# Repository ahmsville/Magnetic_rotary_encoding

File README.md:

# Magnetic_Rotary_Encoding

## Learn more about this project - 
 - https://www.ahmsvillelabs.io/projects/magnetic-rotary-encoding
 - https://youtu.be/atb6d4b-VYk
 - https://youtu.be/_1tGosBLRB0

## BUILD INSTRUCTIONS
 - https://www.ahmsvillelabs.io/magnetic-rotary-encoderbuild

# Hardware Options

 ## 1. Magnetic Rotary Encoder 
 This is standalone encoder made to connect to a seperate microcontroller like an Arduino board, this version has a base resolution of 72, extendable up to 72000 steps per revolution.

 ### Features:
- Capacitive touch / button input
- Addressable Led ring (18 LEDs)
 ### Supported Boards / Platform:
- **All Arduino Boards** 
- **Raspberry Pi Pico C/C++ SDK** 
- **All Micropython-Supported Boards**

## 2. Magnetic Rotary Encoder MINI 
 This is standalone encoder similar to the first option, only with a small form factor, this version has a base resolution of 36, extendable up to 36000 steps per revolution.

  ### Features:
- Capacitive touch / button input
- Addressable Led ring (12 LEDs)
 ### Supported Boards / Platform:
- **All Arduino Boards** 
- **Raspberry Pi Pico C/C++ SDK** 
- **All Micropython-Supported Boards**

## [3. Pico Dev M3](https://github.com/ahmsville/Magnetic_rotary_encoding/tree/master/PICO%20DEV%20M3) 
 This is a full fledged development board combined with the magnetic rotary encoder, its built with the Raspberry Pi RP2040 microcontroller chip with a base resolution of 36, extendable up to 36000 steps per revolution.

  ### Features:
- RP2040 chip, Dual-core Arm Cortex-M0+ processor at 133 MHz
- 264kB on-chip SRAM
- 128Mb on-board QSPI flash
- 19 multifunction GPIO pins, with 2 analog inputs
- 2 UARTs
- 2 SPI controllers
- 2 I2C controllers
- 16 PWM channels
- USB 1.1 controller with host and device support
- 8 PIO state machines
- USB type C
- Lipo charging
- onboard Button input
- Addressable Led ring (18 LEDs)
 ### Supported Platform:
- **RP2040 C/C++ SDK** 
- **Micropython**

# How to connect and use the [Ahmsville labs magnetic rotary encoder](https://www.tindie.com/products/22156/).

There are three ways to connect the magnetic rotary encoder, all with their benefits and draw backs.

## 1. Analog only Detection: 

in this mode the library uses just the signals from the hall effect sensors to make sense of the rotation of the encoder. the benefit of this mode is that you only need two analog pins to do all the rotation encoding, also been analog means you can use the libraries built in interpolation mode for an extremely high and granular resolution. The drawback is, this mode requires constant polling of the sensors which is not ideal for a complex system, also if the board does not have analog pins or if your setup cannot spare any of them, then you cannot use this mode.

## Connection

To use this mode, simply connect ENC-1 and ENC-2 to two analog input pins, you may also connect the LED pin to any available pin on the board. VCC  should be connected to the same voltage level used by the microcontroller on the boards, so power the encoder with 5v if the board uses 5v, and power it with 3.3v it the board uses 3.3v, you should offcus also connect the GND pin.

## Code

To test the example code, all you have to do is activate the analog only mode and change the pin assignment according to your connections. For the mode, you have the option to choose continuous rotation detection which returns a continuous count in either direction, or absolute positioning, which returns a value within the encoder’s base resolution, you can also choose the extended interpolated resolution mode for a super-duper high resolution.

## C/C++

```c++
#define ENCMODE 1 // BASE RESOLUTION ANALOG ONLY
//#define ENCMODE 2 // BASE RESOLUTION ANALOG ONLY ABSOLUTE POSITIONING
//#define ENCMODE 3 // EXTENDED RESOLUTION ANALOG ONLY
//#define ENCMODE 4 // BASE RESOLUTION ANALOG AND DIGITAL
//#define ENCMODE 5 // BASE RESOLUTION ANALOG AND DIGITAL ABSOLUTE POSITIONING
//#define ENCMODE 6 // EXTENDED RESOLUTION ANALOG AND DIGITAL
//#define ENCMODE 7 // BASE RESOLUTION DIGITAL ONLY
//#define ENCMODE 8 // BASE RESOLUTION DIGITAL ONLY ABSOLUTE POSITIONING
```

```c++
#define E1_ADC_PIN 26 // ADC PIN for hall sensor 1
#define E2_ADC_PIN 27 // ADC PIN for hall sensor 2
```

## MicroPython

```python
ENCMODE = 1 # BASE RESOLUTION ANALOG ONLY
#ENCMODE  = 2 # BASE RESOLUTION ANALOG ONLY ABSOLUTE POSITIONING
#ENCMODE  = 3 # EXTENDED RESOLUTION ANALOG ONLY
#ENCMODE  = 4 # BASE RESOLUTION ANALOG AND DIGITAL
#ENCMODE  = 5 # BASE RESOLUTION ANALOG AND DIGITAL ABSOLUTE POSITIONING
#ENCMODE  = 6 # EXTENDED RESOLUTION ANALOG AND DIGITAL
#ENCMODE  = 7 # BASE RESOLUTION DIGITAL ONLY
#ENCMODE  = 8 # BASE RESOLUTION DIGITAL ONLY ABSOLUTE POSITIONING
```

```python
E1_ADC_PIN = 26  # ADC PIN for hall sensor 1
E2_ADC_PIN = 27  # ADC PIN for hall sensor 2
```

## 2. Analog and Digital Detection: 

in this mode the library uses the signals from the hall effect sensors together with two additional digital interrupt enabled input pins. This mode has all the same features and benefits as the analog only detection mode without the need for constant polling of the hall effect sensors, this is extremely usefull for complex systems, as the interrupt pins notify the code of when a rotation occurs, so constant polling is not needed, this mode is in fact the mode used on the [Ahmsville Dial V2](https://youtu.be/yGbshYLfDnc).
Please note that the code will return to constant polling if you select the Extended Resolution mode, since this process requires interpolation between the encoder’s steps.

## Connection

To use this mode, simply connect ENC-1 and ENC-2 to two analog input pins, and E1-INT1 and E2-INT1 to two interrupt enabled pins on the board, you may also connect the LED pin to any available pins on the board. VCC  should be connected to the same voltage level used by the microcontroller on the boards, so power the encoder with 5v if the board uses 5v, and power it with 3.3v it the board uses 3.3v, you should offcus also connect the GND pin.

Depending on your encoder version, you may also need to bridge the config pads on the PCB to use this mode.

## Code

To test the code, all you have to do is activate the analog and digital mode and also change the pin assignment according to your connections. For this mode, you also have the option to choose continuous rotation detection which returns a continuous count in either direction, or absolute positioning, which returns a value within the encoder’s base resolution, you can also choose the extended interpolated resolution mode for a super-duper high resolution.

## C/C++

```c++
//#define ENCMODE 1 // BASE RESOLUTION ANALOG ONLY
//#define ENCMODE 2 // BASE RESOLUTION ANALOG ONLY ABSOLUTE POSITIONING
//#define ENCMODE 3 // EXTENDED RESOLUTION ANALOG ONLY
#define ENCMODE 4 // BASE RESOLUTION ANALOG AND DIGITAL
//#define ENCMODE 5 // BASE RESOLUTION ANALOG AND DIGITAL ABSOLUTE POSITIONING
//#define ENCMODE 6 // EXTENDED RESOLUTION ANALOG AND DIGITAL
//#define ENCMODE 7 // BASE RESOLUTION DIGITAL ONLY
//#define ENCMODE 8 // BASE RESOLUTION DIGITAL ONLY ABSOLUTE POSITIONING
```

```c++
#define E1_INT1 16 // hall sensor 1 interrupt pin 1
#define E2_INT1 18 // hall sensor 2 interrupt pin 1

#define E1_ADC_PIN 26 // ADC PIN for hall sensor 1
#define E2_ADC_PIN 27 // ADC PIN for hall sensor 2
```

## MicroPython

```python
#ENCMODE = 1 # BASE RESOLUTION ANALOG ONLY
#ENCMODE  = 2 # BASE RESOLUTION ANALOG ONLY ABSOLUTE POSITIONING
#ENCMODE  = 3 # EXTENDED RESOLUTION ANALOG ONLY
ENCMODE  = 4 # BASE RESOLUTION ANALOG AND DIGITAL
#ENCMODE  = 5 # BASE RESOLUTION ANALOG AND DIGITAL ABSOLUTE POSITIONING
#ENCMODE  = 6 # EXTENDED RESOLUTION ANALOG AND DIGITAL
#ENCMODE  = 7 # BASE RESOLUTION DIGITAL ONLY
#ENCMODE  = 8 # BASE RESOLUTION DIGITAL ONLY ABSOLUTE POSITIONING
```

```python
E1_INT1 = 16 # hall sensor 1 interrupt pin 1
E2_INT1 = 18 # hall sensor 2 interrupt pin 1

E1_ADC_PIN = 26 # ADC PIN for hall sensor 1
E2_ADC_PIN = 27 # ADC PIN for hall sensor 2
```

## 3. Digital only Detection: 

in this mode the library uses only digital interrupt enabled input pins; four of them. This mode is similar in operation to traditional rotary switches, the analog signals from the hall effect sensors have been converted to digital signals using comparators, so no analog input pins are required. This mode was developed for systems that don’t have or cannot spare analog input pins, its also the fastest mode and requires zero polling, which is why I used it to encode the [Pick N Place Wheel](https://youtu.be/MtNO8-5vCqg). 
Because this mode uses digital signals alone, you cannot use the interpolated extended resolution mode that is available in the previous modes.

## Connection

To use this mode, simply connect E1-INT1, E1-INT2, E2-INT1 and E2-INT2 to four interrupt enabled pins on the board, you may also connect the LED pin to any available pins on the board. VCC  should be connected to the same voltage level used by the microcontroller on the boards, so power the encoder with 5v if the board uses 5v, and power it with 3.3v it the board uses 3.3v,  also connect the GND pin.

## Code

To test the code, all you have to do is activate the digital only mode and also change the pin assignments according to your connections. For this mode, you have the option to choose continuous rotation detection which returns a continuous count in either direction, or absolute positioning, which returns a value within the encoder’s base resolution.

## C/C++

```c++
//#define ENCMODE 1 // BASE RESOLUTION ANALOG ONLY
//#define ENCMODE 2 // BASE RESOLUTION ANALOG ONLY ABSOLUTE POSITIONING
//#define ENCMODE 3 // EXTENDED RESOLUTION ANALOG ONLY
//#define ENCMODE 4 // BASE RESOLUTION ANALOG AND DIGITAL
//#define ENCMODE 5 // BASE RESOLUTION ANALOG AND DIGITAL ABSOLUTE POSITIONING
//#define ENCMODE 6 // EXTENDED RESOLUTION ANALOG AND DIGITAL
#define ENCMODE 7 // BASE RESOLUTION DIGITAL ONLY
//#define ENCMODE 8 // BASE RESOLUTION DIGITAL ONLY ABSOLUTE POSITIONING
```

```c++
#define E1_INT1 16 // hall sensor 1 interrupt pin 1
#define E1_INT2 17 // hall sensor 1 interrupt pin 2
#define E2_INT1 18 // hall sensor 2 interrupt pin 1
#define E2_INT2 19 // hall sensor 2 interrupt pin 2
```

## MicroPython

```python
#ENCMODE = 1 # BASE RESOLUTION ANALOG ONLY
#ENCMODE  = 2 # BASE RESOLUTION ANALOG ONLY ABSOLUTE POSITIONING
#ENCMODE  = 3 # EXTENDED RESOLUTION ANALOG ONLY
ENCMODE  = 4 # BASE RESOLUTION ANALOG AND DIGITAL
#ENCMODE  = 5 # BASE RESOLUTION ANALOG AND DIGITAL ABSOLUTE POSITIONING
#ENCMODE  = 6 # EXTENDED RESOLUTION ANALOG AND DIGITAL
#ENCMODE  = 7 # BASE RESOLUTION DIGITAL ONLY
#ENCMODE  = 8 # BASE RESOLUTION DIGITAL ONLY ABSOLUTE POSITIONING
```

```python
E1_INT1 = 16  # hall sensor 1 interrupt pin 1
E1_INT2 = 17  # hall sensor 1 interrupt pin 2
E2_INT1 = 18  # hall sensor 2 interrupt pin 1
E2_INT2 = 19  # hall sensor 2 interrupt pin 2
```

# Complimentary Input on the Encoder

You have two options when it comes to complimentary input on the encoder, you can choose to use capacitive touch or a normal push button, both the capacitive touch and the push button will be included with the kit if you buy it from [my store](https://www.tindie.com/products/22156/).
To use capacitive touch, you will need an Arduino board, if you use other development boards like the ESP32 or Raspberry PI Pico, you will have to use the push button.

## Capacitive touch
To use the capacitive touch on an Arduino, you must have assembled the encoder according to the instructions, so that you can simply connect CT1 and CT2 to two available pins and then update the pin assignment in the example code accordingly.

## C/C++

```c++
#define CT1 5 // CAPACITIVE TOUCH (CT1)
#define CT2 6 // CAPACITIVE TOUCH (CT2)
```

## Push button
To use the push button, you should solder the included button to the encoder board and then connect only CT1 to an available pin on the development board.

## C/C++

```c++
#define CT1 15 // PUSH BUTTON (CT1)
```

## MicroPython

```python
CT1 = 15 # PUSH BUTTON (CT1)
```

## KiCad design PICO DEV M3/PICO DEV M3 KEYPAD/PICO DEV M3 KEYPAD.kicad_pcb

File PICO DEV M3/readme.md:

# PICO DEV M3

The **Pico Dev M3** is a development board based on Raspberry Pi's **RP2040 microcontrolle**r chip, the board is also a high-resolution **magnetic rotary encoder** when paired with a few 3D printed parts, which makes this the perfect board for applications and projects that can benefit from having a rotary encoder, a good example is making macro pads, and other similar secondary controllers.

## **Board Features**
- RP2040 chip, Dual-core Arm Cortex-M0+ processor at 133 MHz
- 264kB on-chip SRAM
- 128Mb on-board QSPI flash
- 19 multifunction GPIO pins, with 2 analog inputs
- 2 UARTs
- 2 SPI controllers
- 2 I2C controllers
- 16 PWM channels
- USB 1.1 controller with host and device support
- 8 PIO state machines
- USB type C
- Lipo charging
- onboard Button input
- Addressable Led ring (18 LEDs)

## **Encoder Features**

- The onboard encoder features a base resolution of **36 steps, extending up to 36000** steps per revolution.
- There’s also a ring of **18 individually addressable LEDs** on board.
- Features a ball bearing which gives the encoder a significantly smoother feel compared to traditional rotary encoders.
- Customizable 3d printed encoder. 
- Implementing the encoder is also really straightforward using the dedicated Libraries and Sample Codes
- Easy mounting options

### **Programming Language:**

- **RP2040 C/C++ SDK** 
- **Micropython**

## **Sample Projects Based on the PICO DEV M3:**

- **Pico Dev M3 Keypad** 

This is a 12-key macropod that uses the Pico dev m3 as its controller, the breakout board features backlit keys, headers for connecting I2C, SPI, and UART peripherals, and a header for connecting a joystick module to the Pico dev m3, you can power the keypad from the type c port on the pico dev m3 board or with a Lipo battery connected to the BAT header, taking advantage of the Lipo charge controller built into the pico dev m3.
- **PIO Stepper Controller**

This breakout board allows you to use this Programmable IO (PIO) on the RP2040 chip on the Pico dev m3 to individually control 3 stepper motors. This board can be used to control any 3-axis motion system, robot, or custom mechanism.

## BUILD INSTRUCTIONS
 - https://www.ahmsvillelabs.io/magnetic-rotary-encoderbuild/pico-dev-m3

### **Encoder Assembly:**

- Sandwich the pico dev m3 board between the **BOARD BUTTON** and **BOARD TOP** 3D printed parts, and secure them together using 3 **M1.4x6mm** self-tapping screws.

- Attach **608 bearing (8x22x7)** to the assembly and secure it with the **BEARING HOLDER** part and 1 **M2x8mm** self-tapping screw.

- Install **(18pcs) 3x1mm** neodymium magnets to the KNOB in an alternating pole configuration.
Depending on your 3D printer's tolerance you may use super glue to secure the magnets, but if the holes turn out as the perfect size, a simple press-fit is sufficient.

- Attach the knob to the bearing.

- For Flexibility, you may print the **BUTTON BASE** file this allows the pico dev m3 encoder and button to be used conviniently, the button base attaches to the pico dev encoder via 2 **M2x8mm** selftapping screws.

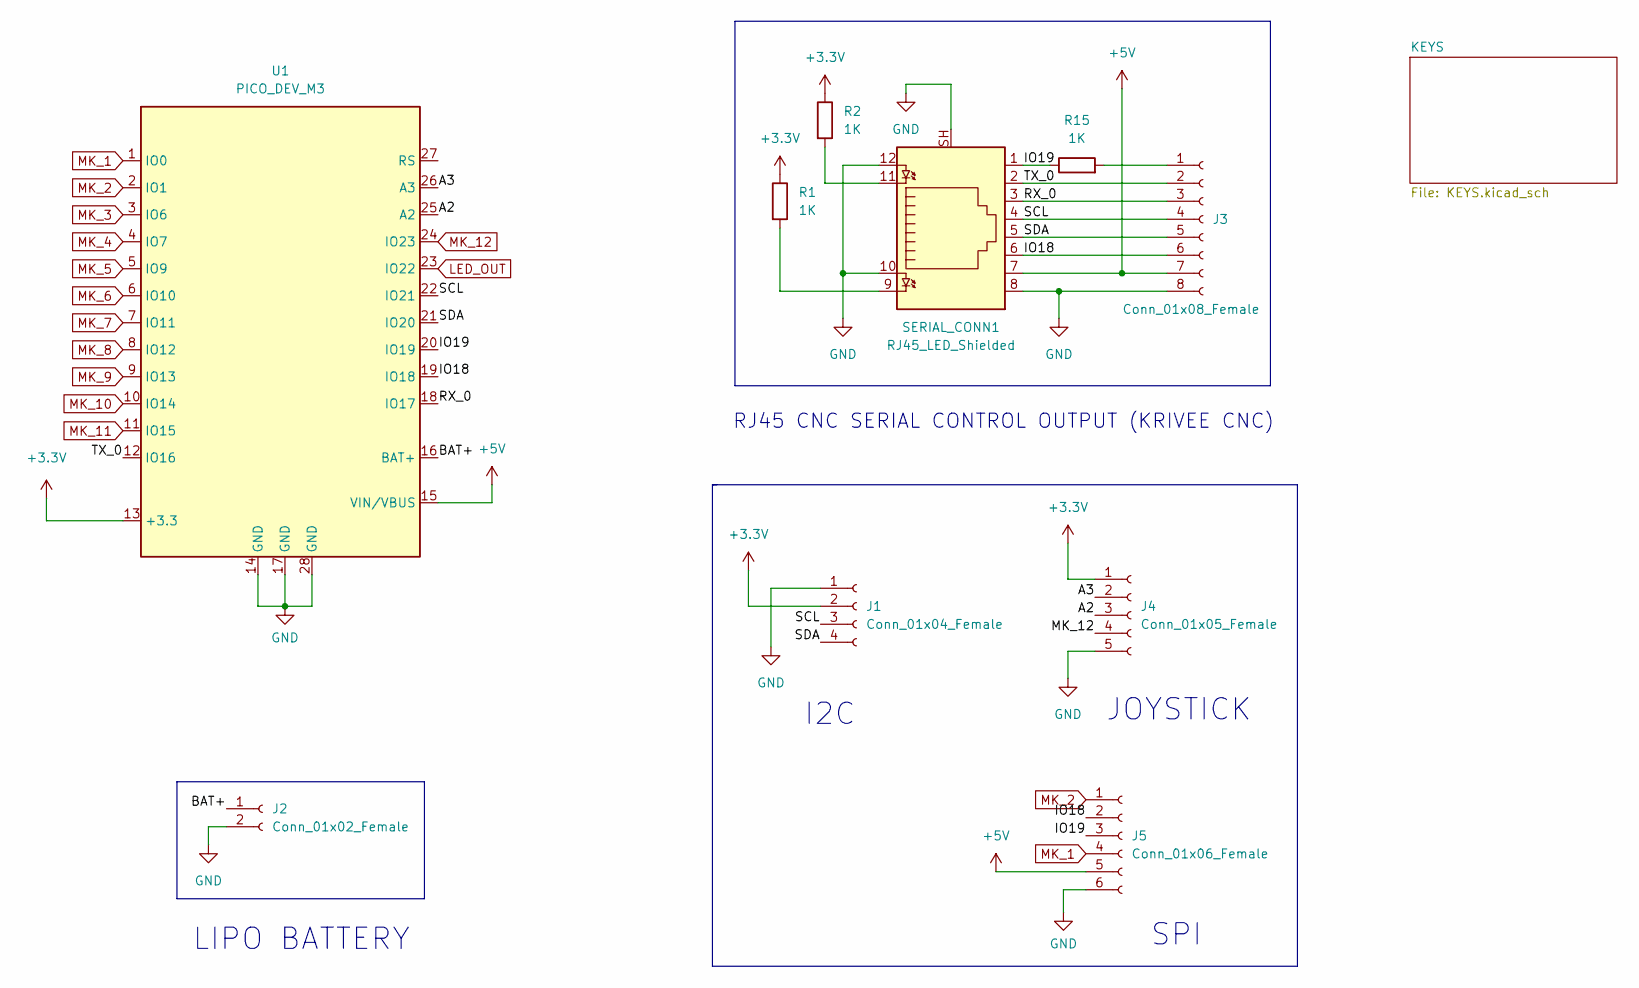
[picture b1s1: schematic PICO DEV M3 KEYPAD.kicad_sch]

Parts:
J1: Conn_01x04_Female; PinSocket_1x04_P2.54mm_Vertical
J2: Conn_01x02_Female; PinSocket_1x02_P2.54mm_Vertical
J3: Conn_01x08_Female; PinSocket_1x08_P2.54mm_Vertical
J4: Conn_01x05_Female; PinSocket_1x05_P2.54mm_Vertical
J5: Conn_01x06_Female; PinSocket_1x06_P2.54mm_Vertical
R1, R2, R15: 1K; R_0603_1608Metric
SERIAL_CONN1: RJ45_LED_Shielded; RJ45_LED_SHIELDED
U1: PICO_DEV_M3; PICO DEV M3

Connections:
+3.3V: J1.2, J4.1, R1.1, R2.1, U1.13 (+3.3); also elsewhere on the board
+5V: J3.7, J5.5, SERIAL_CONN1.7, U1.15 (VIN/VBUS)
/A2: J4.3, U1.25 (A2)
/A3: J4.2, U1.26 (A3)
/BAT+: J2.1, U1.16 (BAT+)
/IO18: J3.6, J5.2, SERIAL_CONN1.6, U1.19 (IO18)
/IO19: J5.3, R15.1, SERIAL_CONN1.1, U1.20 (IO19)
/RX_0: J3.3, SERIAL_CONN1.3, U1.18 (IO17)
/SCL: J1.3, J3.4, SERIAL_CONN1.4, U1.22 (IO21)
/SDA: J1.4, J3.5, SERIAL_CONN1.5, U1.21 (IO20)
/TX_0: J3.2, SERIAL_CONN1.2, U1.12 (IO16)
GND: J1.1, J2.2, J3.8, J4.5, J5.6, SERIAL_CONN1.8, SERIAL_CONN1.10, SERIAL_CONN1.12, SERIAL_CONN1.SH, U1.14 (GND), U1.17 (GND), U1.28 (GND); also elsewhere on the board
LED_OUT: U1.23 (IO22); also elsewhere on the board
MK_1: J5.4, U1.1 (IO0); also elsewhere on the board
MK_2: J5.1, U1.2 (IO1); also elsewhere on the board
MK_3: U1.3 (IO6); also elsewhere on the board
MK_4: U1.4 (IO7); also elsewhere on the board
MK_5: U1.5 (IO9); also elsewhere on the board
MK_6: U1.6 (IO10); also elsewhere on the board
MK_7: U1.7 (IO11); also elsewhere on the board
MK_8: U1.8 (IO12); also elsewhere on the board
MK_9: U1.9 (IO13); also elsewhere on the board
MK_10: U1.10 (IO14); also elsewhere on the board
MK_11: U1.11 (IO15); also elsewhere on the board
MK_12: J4.4, U1.24 (IO23); also elsewhere on the board
unnamed: J3.1, R15.2
unnamed: R1.2, SERIAL_CONN1.9
unnamed: R2.2, SERIAL_CONN1.11

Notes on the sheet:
LIPO BATTERY
JOYSTICK
RJ45 CNC SERIAL CONTROL OUTPUT (KRIVEE CNC)
I2C
SPI

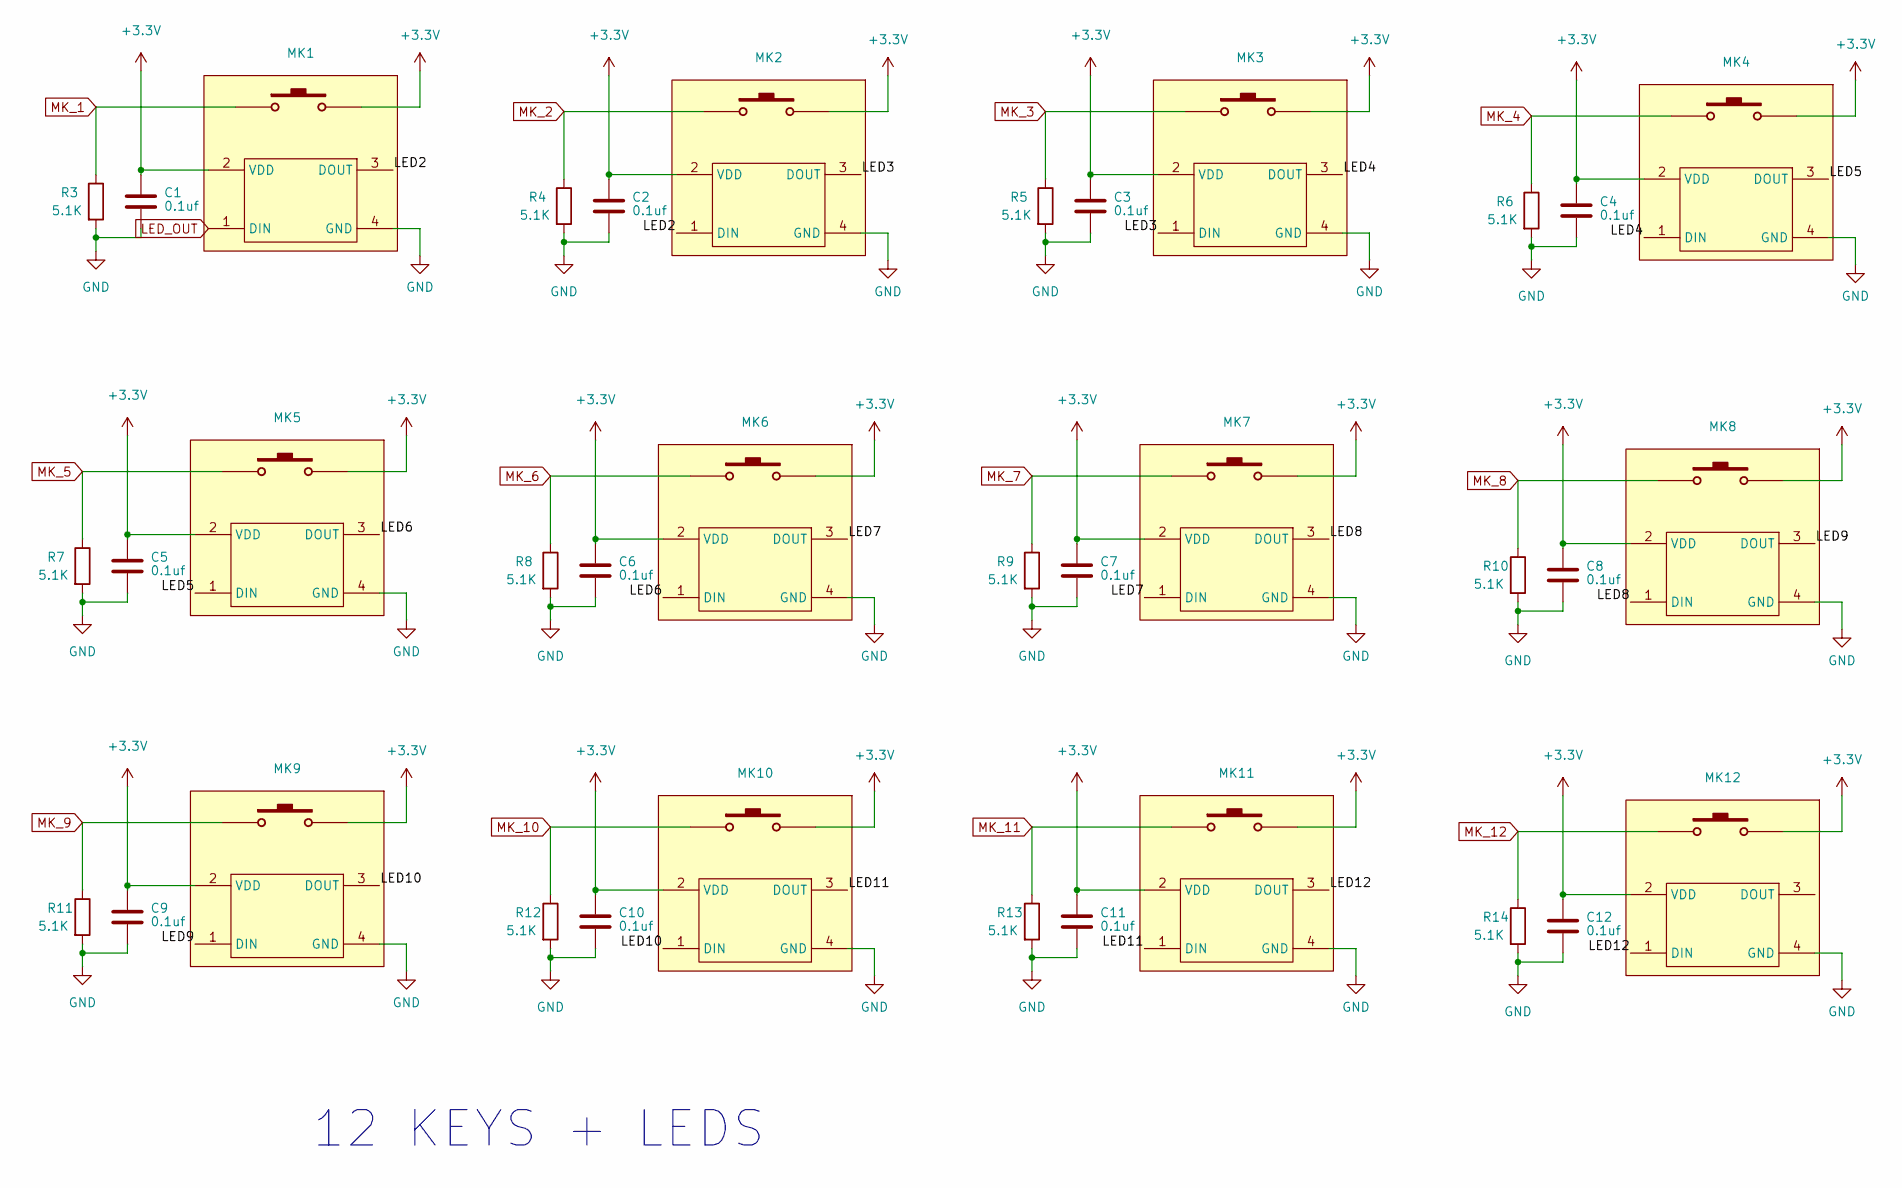
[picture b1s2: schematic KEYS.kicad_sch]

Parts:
C1, C2, C3, C4, C5, C6, C7, C8, C9, C10, C11, C12: 0.1uf; C_0603_1608Metric
MK1, MK2, MK3, MK4, MK5, MK6, MK7, MK8, MK9, MK10, MK11, MK12: Gateron_Switch; GATERON SWITCH
R3, R4, R5, R6, R7, R8, R9, R10, R11, R12, R13, R14: 5.1K; R_0603_1608Metric

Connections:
+3.3V: C1.1, C2.1, C3.1, C4.1, C5.1, C6.1, C7.1, C8.1, C9.1, C10.1, C11.1, C12.1, MK1.2 (VDD), MK1.6, MK2.2 (VDD), MK2.6, MK3.2 (VDD), MK3.6, MK4.2 (VDD), MK4.6, MK5.2 (VDD), MK5.6, MK6.2 (VDD), MK6.6, MK7.2 (VDD), MK7.6, MK8.2 (VDD), MK8.6, MK9.2 (VDD), MK9.6, MK10.2 (VDD), MK10.6, MK11.2 (VDD), MK11.6, MK12.2 (VDD), MK12.6; also elsewhere on the board
/KEYS/LED2: MK1.3 (DOUT), MK2.1 (DIN)
/KEYS/LED3: MK2.3 (DOUT), MK3.1 (DIN)
/KEYS/LED4: MK3.3 (DOUT), MK4.1 (DIN)
/KEYS/LED5: MK4.3 (DOUT), MK5.1 (DIN)
/KEYS/LED6: MK5.3 (DOUT), MK6.1 (DIN)
/KEYS/LED7: MK6.3 (DOUT), MK7.1 (DIN)
/KEYS/LED8: MK7.3 (DOUT), MK8.1 (DIN)
/KEYS/LED9: MK8.3 (DOUT), MK9.1 (DIN)
/KEYS/LED10: MK9.3 (DOUT), MK10.1 (DIN)
/KEYS/LED11: MK10.3 (DOUT), MK11.1 (DIN)
/KEYS/LED12: MK11.3 (DOUT), MK12.1 (DIN)
GND: C1.2, C2.2, C3.2, C4.2, C5.2, C6.2, C7.2, C8.2, C9.2, C10.2, C11.2, C12.2, MK1.4 (GND), MK2.4 (GND), MK3.4 (GND), MK4.4 (GND), MK5.4 (GND), MK6.4 (GND), MK7.4 (GND), MK8.4 (GND), MK9.4 (GND), MK10.4 (GND), MK11.4 (GND), MK12.4 (GND), R3.2, R4.2, R5.2, R6.2, R7.2, R8.2, R9.2, R10.2, R11.2, R12.2, R13.2, R14.2; also elsewhere on the board
LED_OUT: MK1.1 (DIN); also elsewhere on the board
MK_1: MK1.5, R3.1; also elsewhere on the board
MK_2: MK2.5, R4.1; also elsewhere on the board
MK_3: MK3.5, R5.1; also elsewhere on the board
MK_4: MK4.5, R6.1; also elsewhere on the board
MK_5: MK5.5, R7.1; also elsewhere on the board
MK_6: MK6.5, R8.1; also elsewhere on the board
MK_7: MK7.5, R9.1; also elsewhere on the board
MK_8: MK8.5, R10.1; also elsewhere on the board
MK_9: MK9.5, R11.1; also elsewhere on the board
MK_10: MK10.5, R12.1; also elsewhere on the board
MK_11: MK11.5, R13.1; also elsewhere on the board
MK_12: MK12.5, R14.1; also elsewhere on the board

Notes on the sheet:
12 KEYS + LEDS

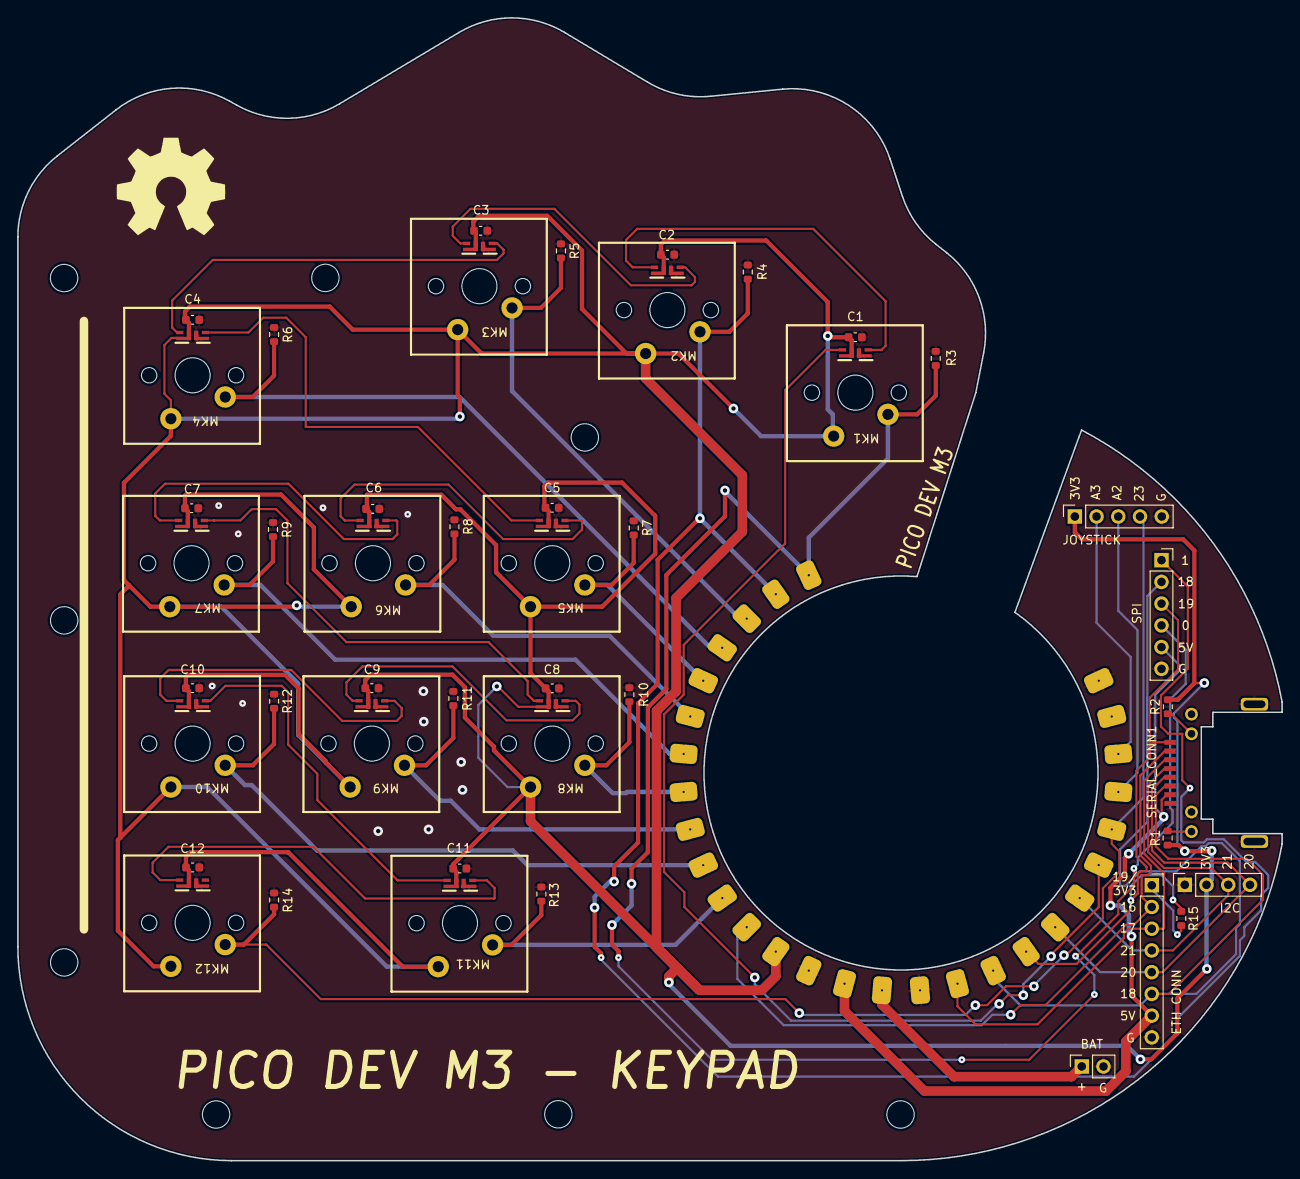
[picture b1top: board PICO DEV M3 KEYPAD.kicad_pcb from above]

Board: 2 copper layers, 147.8 x 133.6 mm, 46 parts (0 on the bottom side), 39 nets.

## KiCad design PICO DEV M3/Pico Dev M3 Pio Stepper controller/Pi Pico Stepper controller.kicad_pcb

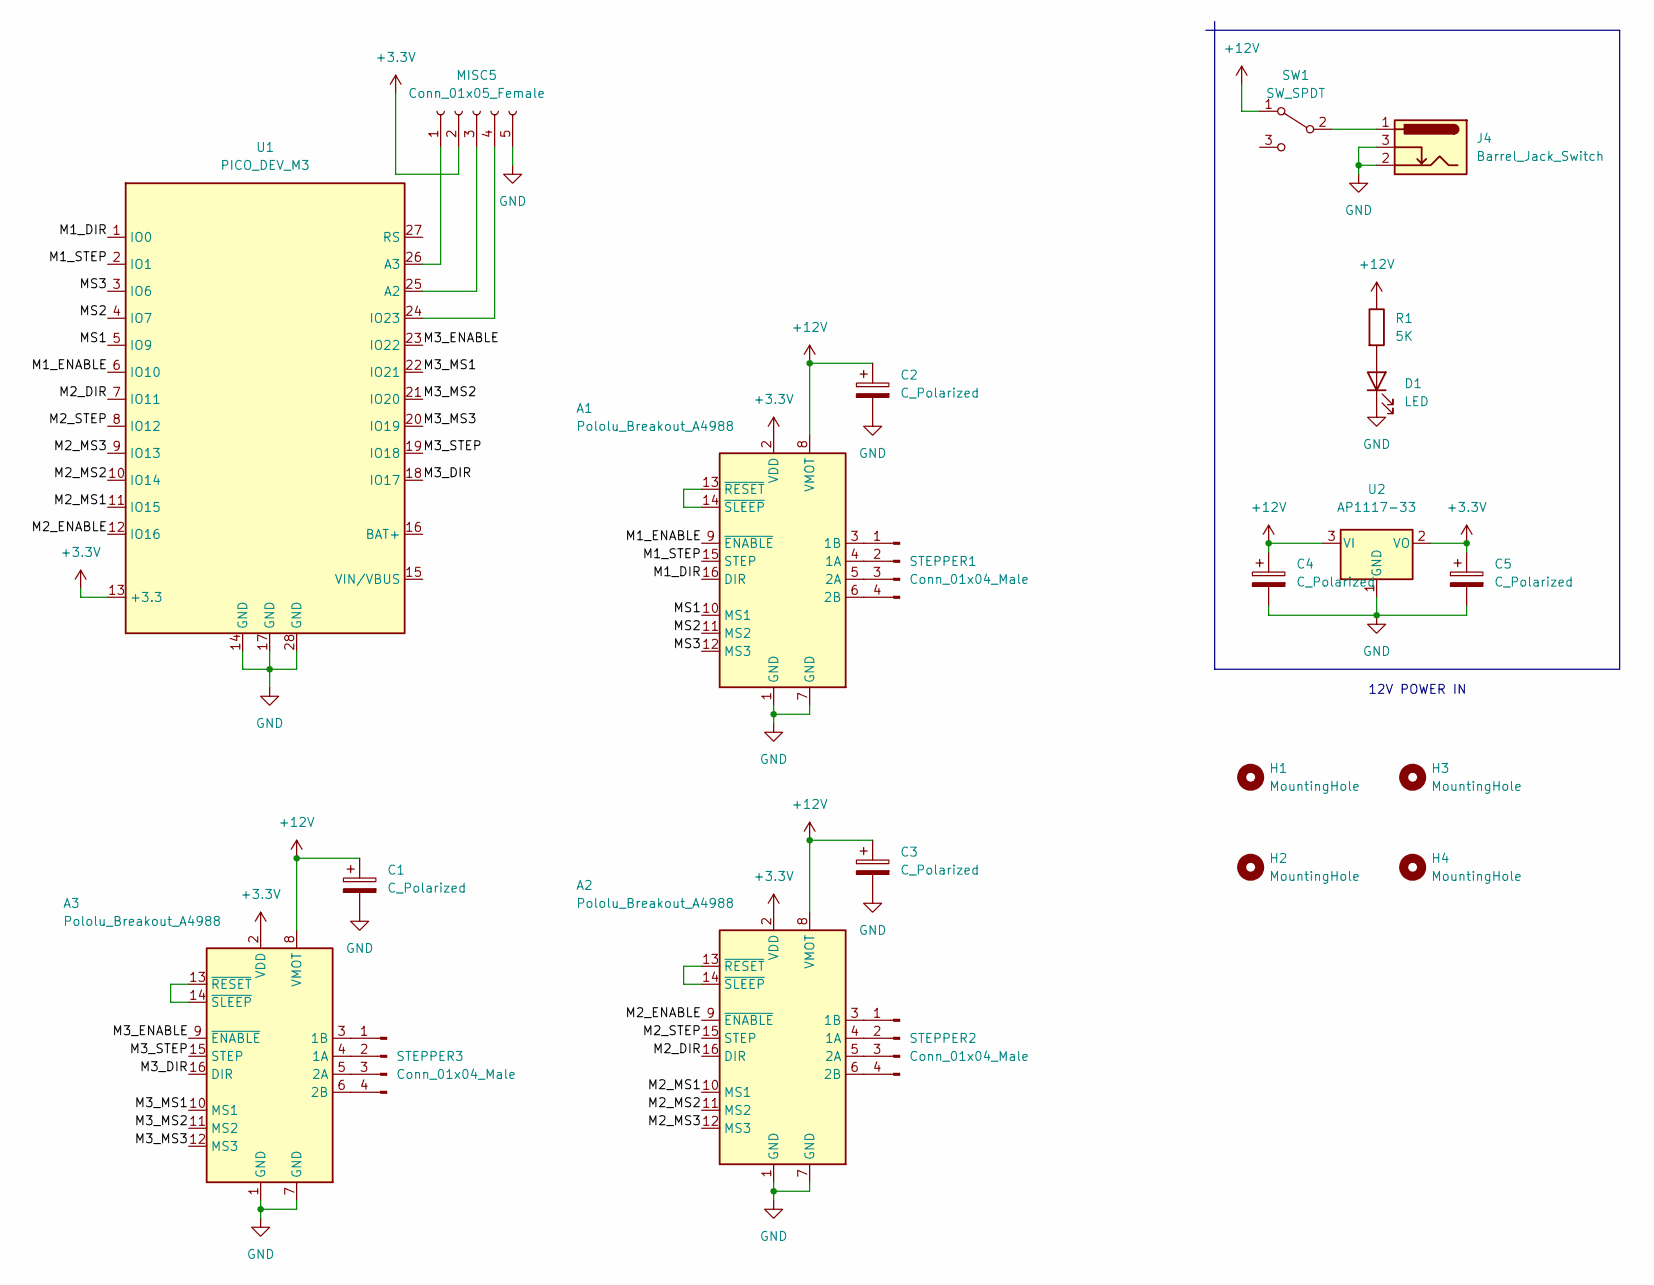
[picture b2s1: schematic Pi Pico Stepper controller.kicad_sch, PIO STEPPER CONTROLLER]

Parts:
A1, A2, A3: Pololu_Breakout_A4988; Pololu_Breakout-16_15.2x20.3mm
C1, C2, C3, C4, C5: C_Polarized; CP_Elec_4x5.4
D1: LED; LED_0603_1608Metric
H1, H2, H3, H4: MountingHole; MountingHole_2.2mm_M2
J4: Barrel_Jack_Switch; BarrelJack_Horizontal
MISC5: Conn_01x05_Female; PinSocket_1x05_P2.54mm_Vertical
R1: 5K; R_0603_1608Metric
STEPPER1, STEPPER2, STEPPER3: Conn_01x04_Male; PinHeader_1x04_P2.54mm_Vertical
SW1: SW_SPDT; SW_SPDT_PCM12
U1: PICO_DEV_M3; PICO DEV M3
U2: AP1117-33; SOT-223-3_TabPin2

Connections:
+3.3V: A1.2 (VDD), A2.2 (VDD), A3.2 (VDD), C5.1, MISC5.2, U1.13 (+3.3), U2.2 (VO)
+12V: A1.8 (VMOT), A2.8 (VMOT), A3.8 (VMOT), C1.1, C2.1, C3.1, C4.1, R1.1, SW1.1 (A), U2.3 (VI)
/M1_DIR: A1.16 (DIR), U1.1 (IO0)
/M1_ENABLE: A1.9 (~ENABLE), U1.6 (IO10)
/M1_STEP: A1.15 (STEP), U1.2 (IO1)
/M2_DIR: A2.16 (DIR), U1.7 (IO11)
/M2_ENABLE: A2.9 (~ENABLE), U1.12 (IO16)
/M2_MS1: A2.10 (MS1), U1.11 (IO15)
/M2_MS2: A2.11 (MS2), U1.10 (IO14)
/M2_MS3: A2.12 (MS3), U1.9 (IO13)
/M2_STEP: A2.15 (STEP), U1.8 (IO12)
/M3_DIR: A3.16 (DIR), U1.18 (IO17)
/M3_ENABLE: A3.9 (~ENABLE), U1.23 (IO22)
/M3_MS1: A3.10 (MS1), U1.22 (IO21)
/M3_MS2: A3.11 (MS2), U1.21 (IO20)
/M3_MS3: A3.12 (MS3), U1.20 (IO19)
/M3_STEP: A3.15 (STEP), U1.19 (IO18)
/MS1: A1.10 (MS1), U1.5 (IO9)
/MS2: A1.11 (MS2), U1.4 (IO7)
/MS3: A1.12 (MS3), U1.3 (IO6)
GND: A1.1 (GND), A1.7 (GND), A2.1 (GND), A2.7 (GND), A3.1 (GND), A3.7 (GND), C1.2, C2.2, C3.2, C4.2, C5.2, D1.1 (K), J4.2, J4.3, MISC5.5, U1.14 (GND), U1.17 (GND), U1.28 (GND), U2.1 (GND)
unnamed: A1.3 (1B), STEPPER1.1
unnamed: A1.4 (1A), STEPPER1.2
unnamed: A1.5 (2A), STEPPER1.3
unnamed: A1.6 (2B), STEPPER1.4
unnamed: A1.13 (~RESET), A1.14 (~SLEEP)
unnamed: A2.3 (1B), STEPPER2.1
unnamed: A2.4 (1A), STEPPER2.2
unnamed: A2.5 (2A), STEPPER2.3
unnamed: A2.6 (2B), STEPPER2.4
unnamed: A2.13 (~RESET), A2.14 (~SLEEP)
unnamed: A3.3 (1B), STEPPER3.1
unnamed: A3.4 (1A), STEPPER3.2
unnamed: A3.5 (2A), STEPPER3.3
unnamed: A3.6 (2B), STEPPER3.4
unnamed: A3.13 (~RESET), A3.14 (~SLEEP)
unnamed: D1.2 (A), R1.2
unnamed: J4.1, SW1.2 (B)
unnamed: MISC5.1, U1.26 (A3)
unnamed: MISC5.3, U1.25 (A2)
unnamed: MISC5.4, U1.24 (IO23)

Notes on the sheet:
12V POWER IN

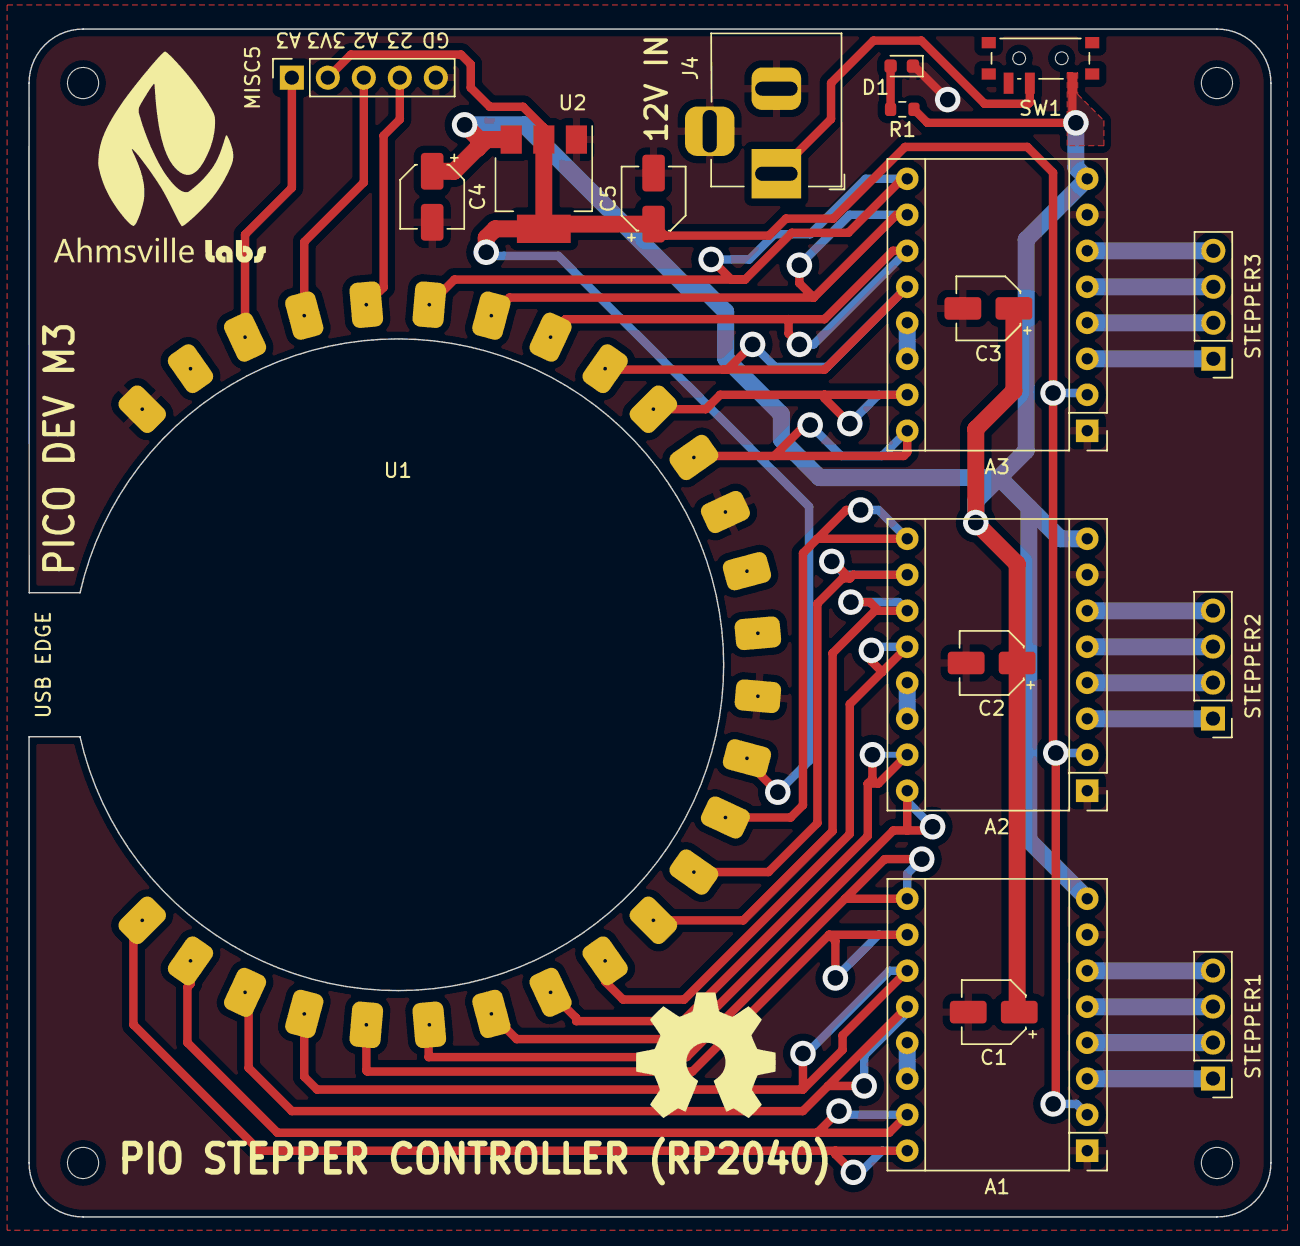
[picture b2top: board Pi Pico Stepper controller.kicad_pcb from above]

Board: 2 copper layers, 87.6 x 83.8 mm, 22 parts (0 on the bottom side), 41 nets.

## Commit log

2021-08-17 Improved detection
2021-08-17 Confirm changes
2022-06-14 Create gitkeep
